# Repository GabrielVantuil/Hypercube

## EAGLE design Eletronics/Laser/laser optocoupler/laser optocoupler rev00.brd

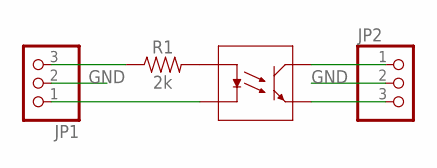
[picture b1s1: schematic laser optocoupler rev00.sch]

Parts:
JP1, JP2: PINHD-1X3; 1X03
R1: 2k; 0603
U$1: PS2701; SOP_4PIN

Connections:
GND: JP1.2, JP2.2
unnamed: R1.2, U$1.1
unnamed: JP1.3, R1.1
unnamed: JP1.1, U$1.2
unnamed: JP2.1, U$1.4
unnamed: JP2.3, U$1.3

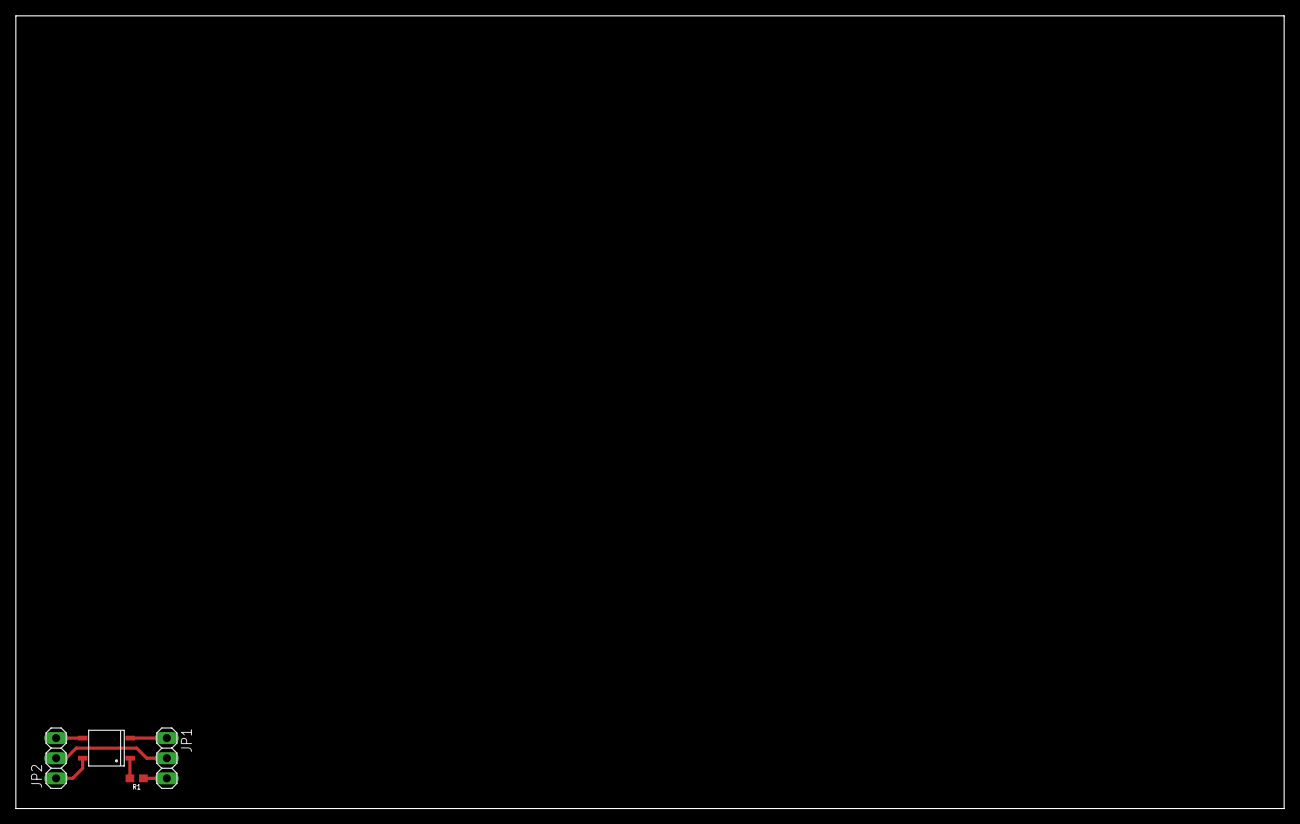
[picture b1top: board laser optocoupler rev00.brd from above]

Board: 2 copper layers, 160.0 x 100.0 mm, 4 parts (0 on the bottom side), 6 nets.

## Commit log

2025-11-13 Reorganizing in a new repository

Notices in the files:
parts and their libraries:
SparkFun-Resistors: Licensing: Creative Commons ShareAlike 4.0 International - https://creativecommons.org/licenses/by-sa/4.0
